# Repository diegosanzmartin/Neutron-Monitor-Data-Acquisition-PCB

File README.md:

# Neutron-Monitor-Data-Acquisition-PCB

New Version made with EasyEDA

## PCB

## Squematic

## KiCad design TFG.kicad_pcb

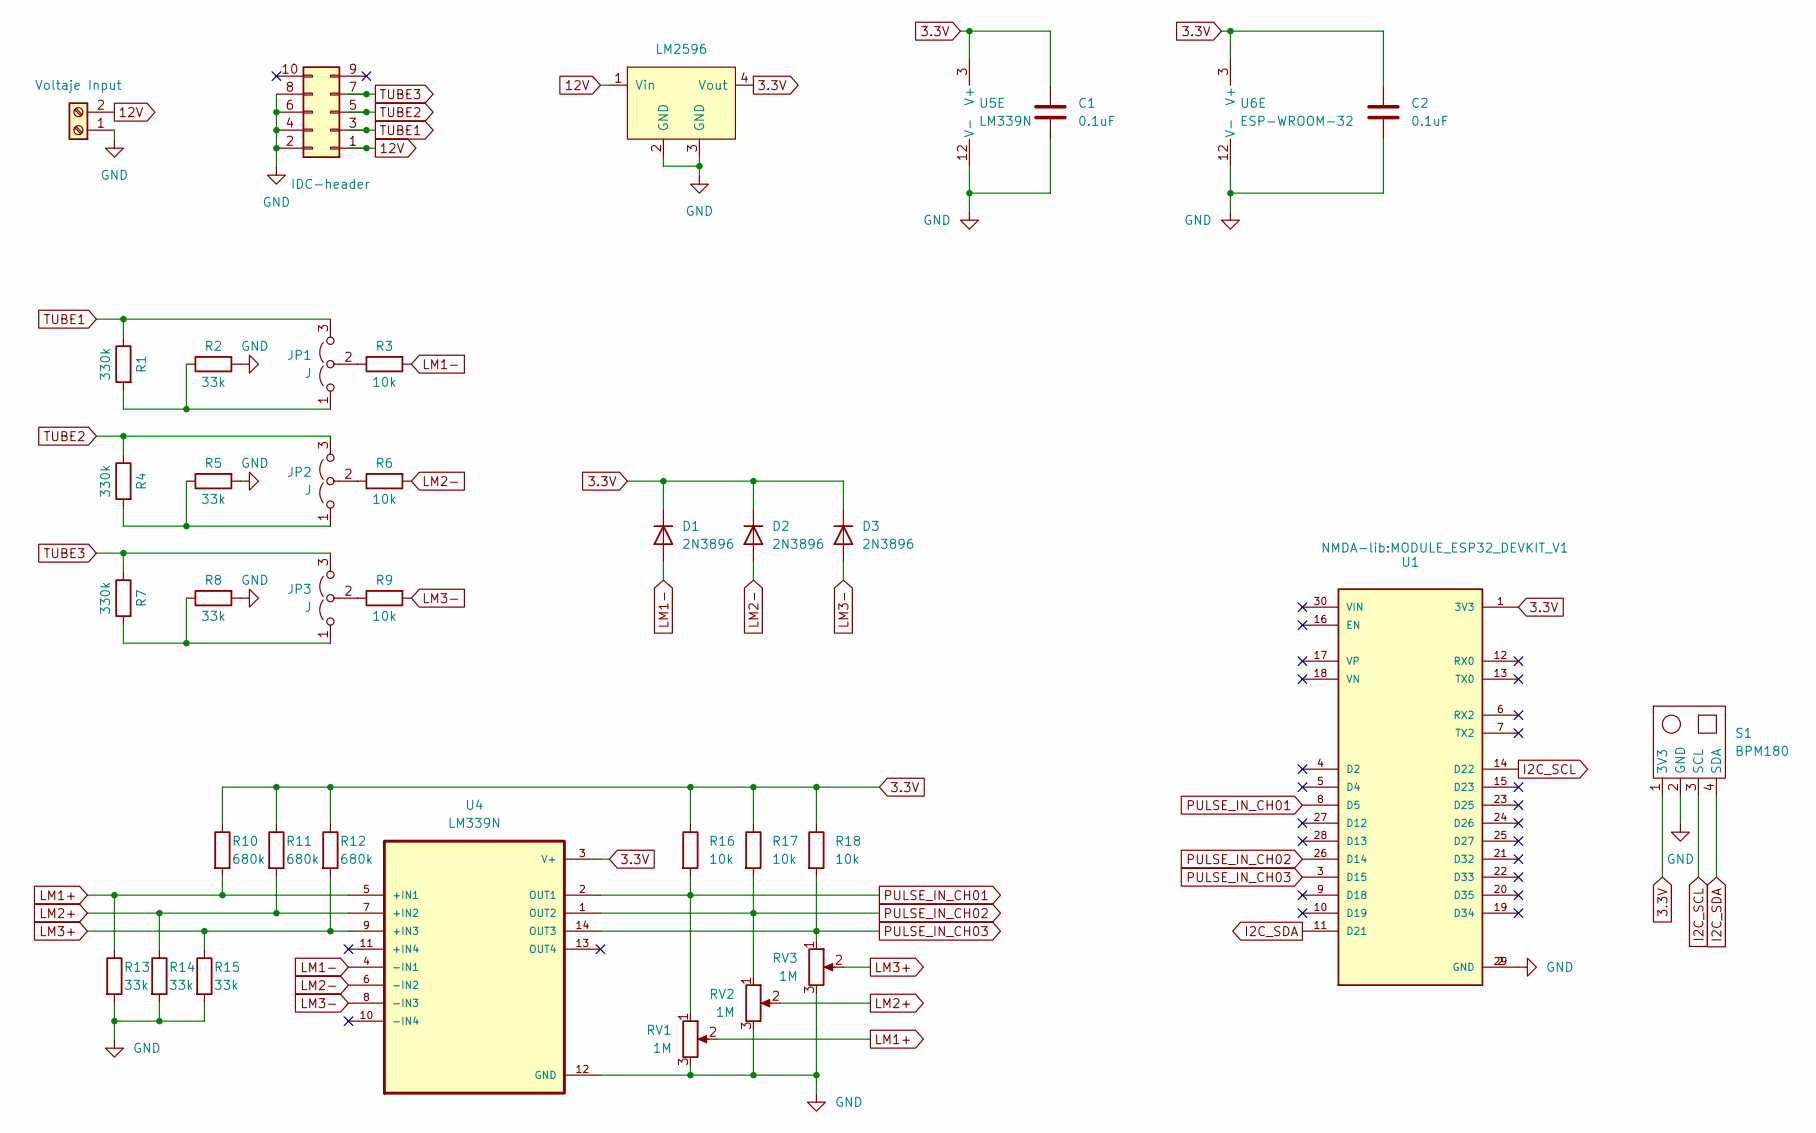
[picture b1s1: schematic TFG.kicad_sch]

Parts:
C1, C2: 0.1uF; Capacitor
D1, D2, D3: 2N3896; D_DO-41_SOD81_P10.16mm_Horizontal
J1: Voltaje Input; TerminalBlock_Altech_AK300-2_P5.00mm
J2: IDC-header; IDC-Header_2x05-1MP_P2.54mm_Latch6.5mm_Vertical
JP1, JP2, JP3: J
R1, R4, R7: 330k; R
R2, R5, R8, R13, R14, R15: 33k; R
R3, R6, R9, R16, R17, R18: 10k; R
R10, R11, R12: 680k; R
RV1, RV2, RV3: 1M; TRIM_3296W-1-254LF
S1: BPM180; BMP180
U1: ESP32-DEVKIT-V1; MODULE_ESP32_DEVKIT_V1; PARTREV N/A
U2: LM2596; DCDC_StepDown_LM2596
U4: LM339N; LM339
U5: LM339N
U6: ESP-WROOM-32

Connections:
3.3V: C1.1, C2.1, D1.1 (K), D2.1 (K), D3.1 (K), R10.1, R11.1, R12.1, R16.1, R17.1, R18.1, S1.1 (3V3), U1.1 (3V3), U2.4 (Vout), U4.3 (V+), U5.3 (V+), U6.3 (V+)
12V: J1.2, J2.1, U2.1 (Vin)
GND: C1.2, C2.2, J1.1, J2.2, J2.4, J2.6, J2.8, R2.2, R5.2, R8.2, R13.2, R14.2, R15.2, RV1.3, RV2.3, RV3.3, S1.2 (GND), U1.2 (GND), U1.29 (GND), U2.2 (GND), U2.3 (GND), U4.12 (GND), U5.12 (V-), U6.12 (V-)
I2C_SCL: S1.3 (SCL), U1.14 (D22)
I2C_SDA: S1.4 (SDA), U1.11 (D21)
LM1+: R10.2, R13.1, RV1.2, U4.5 (+IN1)
LM1-: D1.2 (A), R3.2, U4.4 (-IN1)
LM2+: R11.2, R14.1, RV2.2, U4.7 (+IN2)
LM2-: D2.2 (A), R6.2, U4.6 (-IN2)
LM3+: R12.2, R15.1, RV3.2, U4.9 (+IN3)
LM3-: D3.2 (A), R9.2, U4.8 (-IN3)
unnamed: JP1.1 (A), R1.2, R2.1
unnamed: JP1.2 (C), R3.1
unnamed: JP2.1 (A), R4.2, R5.1
unnamed: JP2.2 (C), R6.1
unnamed: JP3.1 (A), R7.2, R8.1
unnamed: JP3.2 (C), R9.1
PULSE_IN_CH01: R16.2, RV1.1, U1.8 (D5), U4.2 (OUT1)
PULSE_IN_CH02: R17.2, RV2.1, U1.26 (D14), U4.1 (OUT2)
PULSE_IN_CH03: R18.2, RV3.1, U1.3 (D15), U4.14 (OUT3)
TUBE1: J2.3, JP1.3 (B), R1.1
TUBE2: J2.5, JP2.3 (B), R4.1
TUBE3: J2.7, JP3.3 (B), R7.1

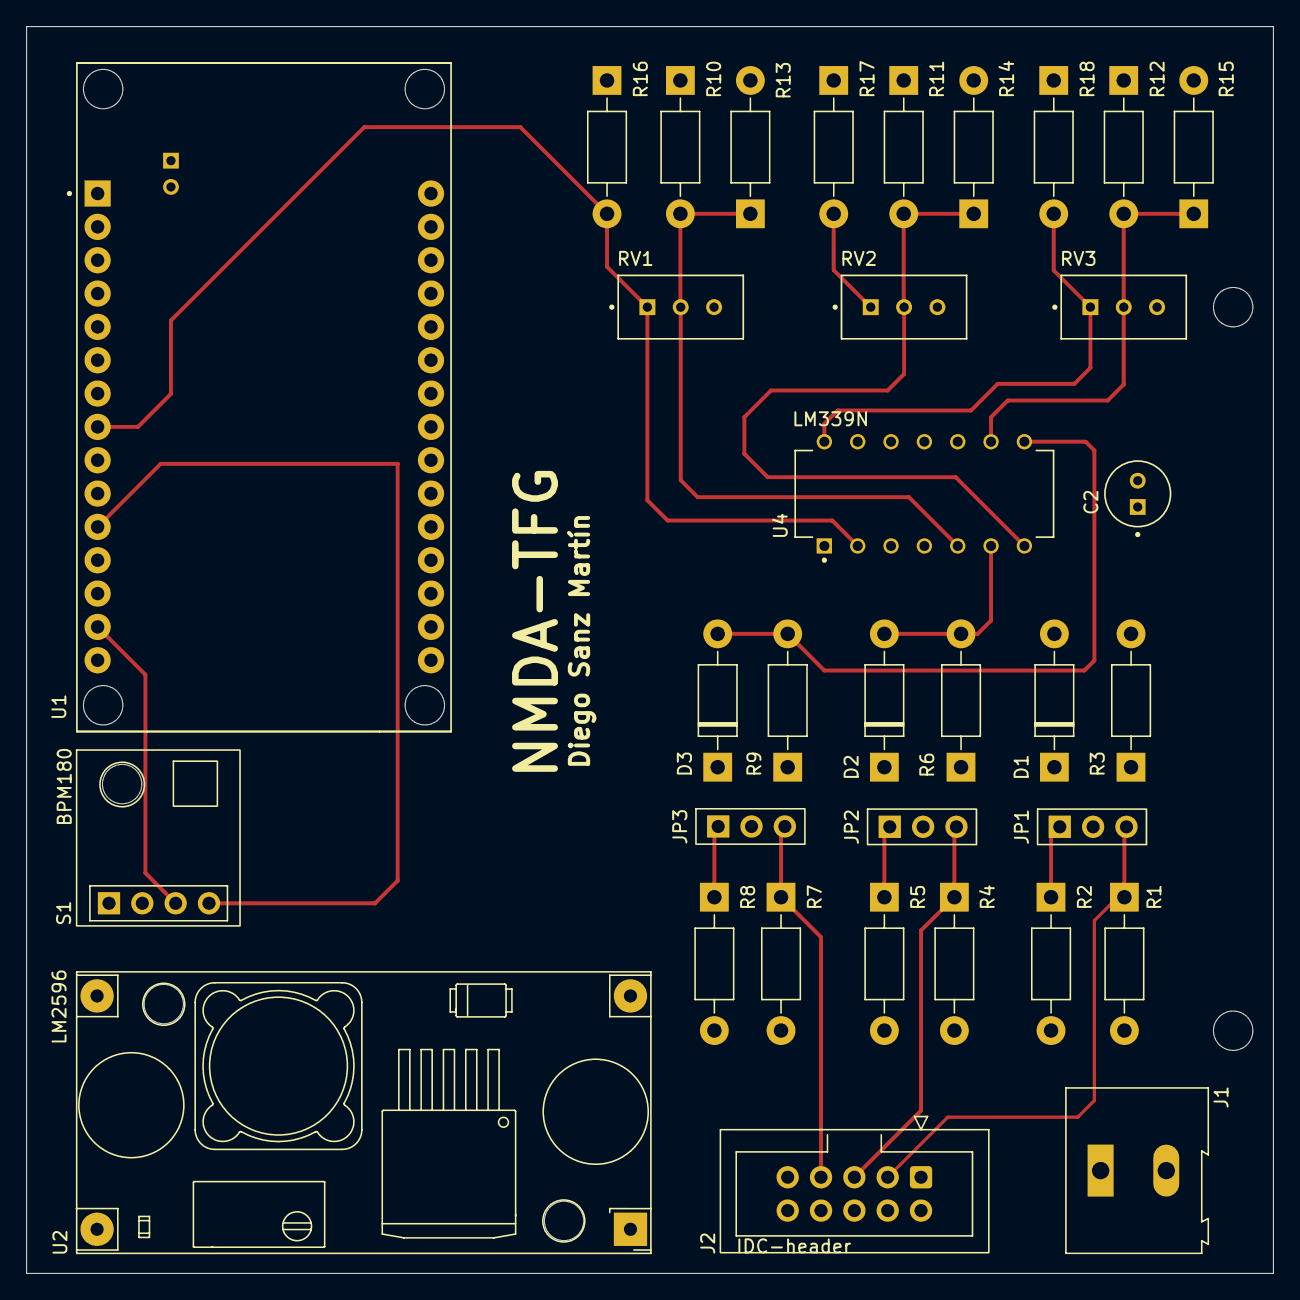
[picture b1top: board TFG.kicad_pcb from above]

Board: 4 copper layers, 95.0 x 95.0 mm, 35 parts (1 on the bottom side), 23 nets.

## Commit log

2022-07-12 update R and RV
2022-07-12 update sq
2022-07-15 Update PCB 95x95mm
2023-04-27 New version
